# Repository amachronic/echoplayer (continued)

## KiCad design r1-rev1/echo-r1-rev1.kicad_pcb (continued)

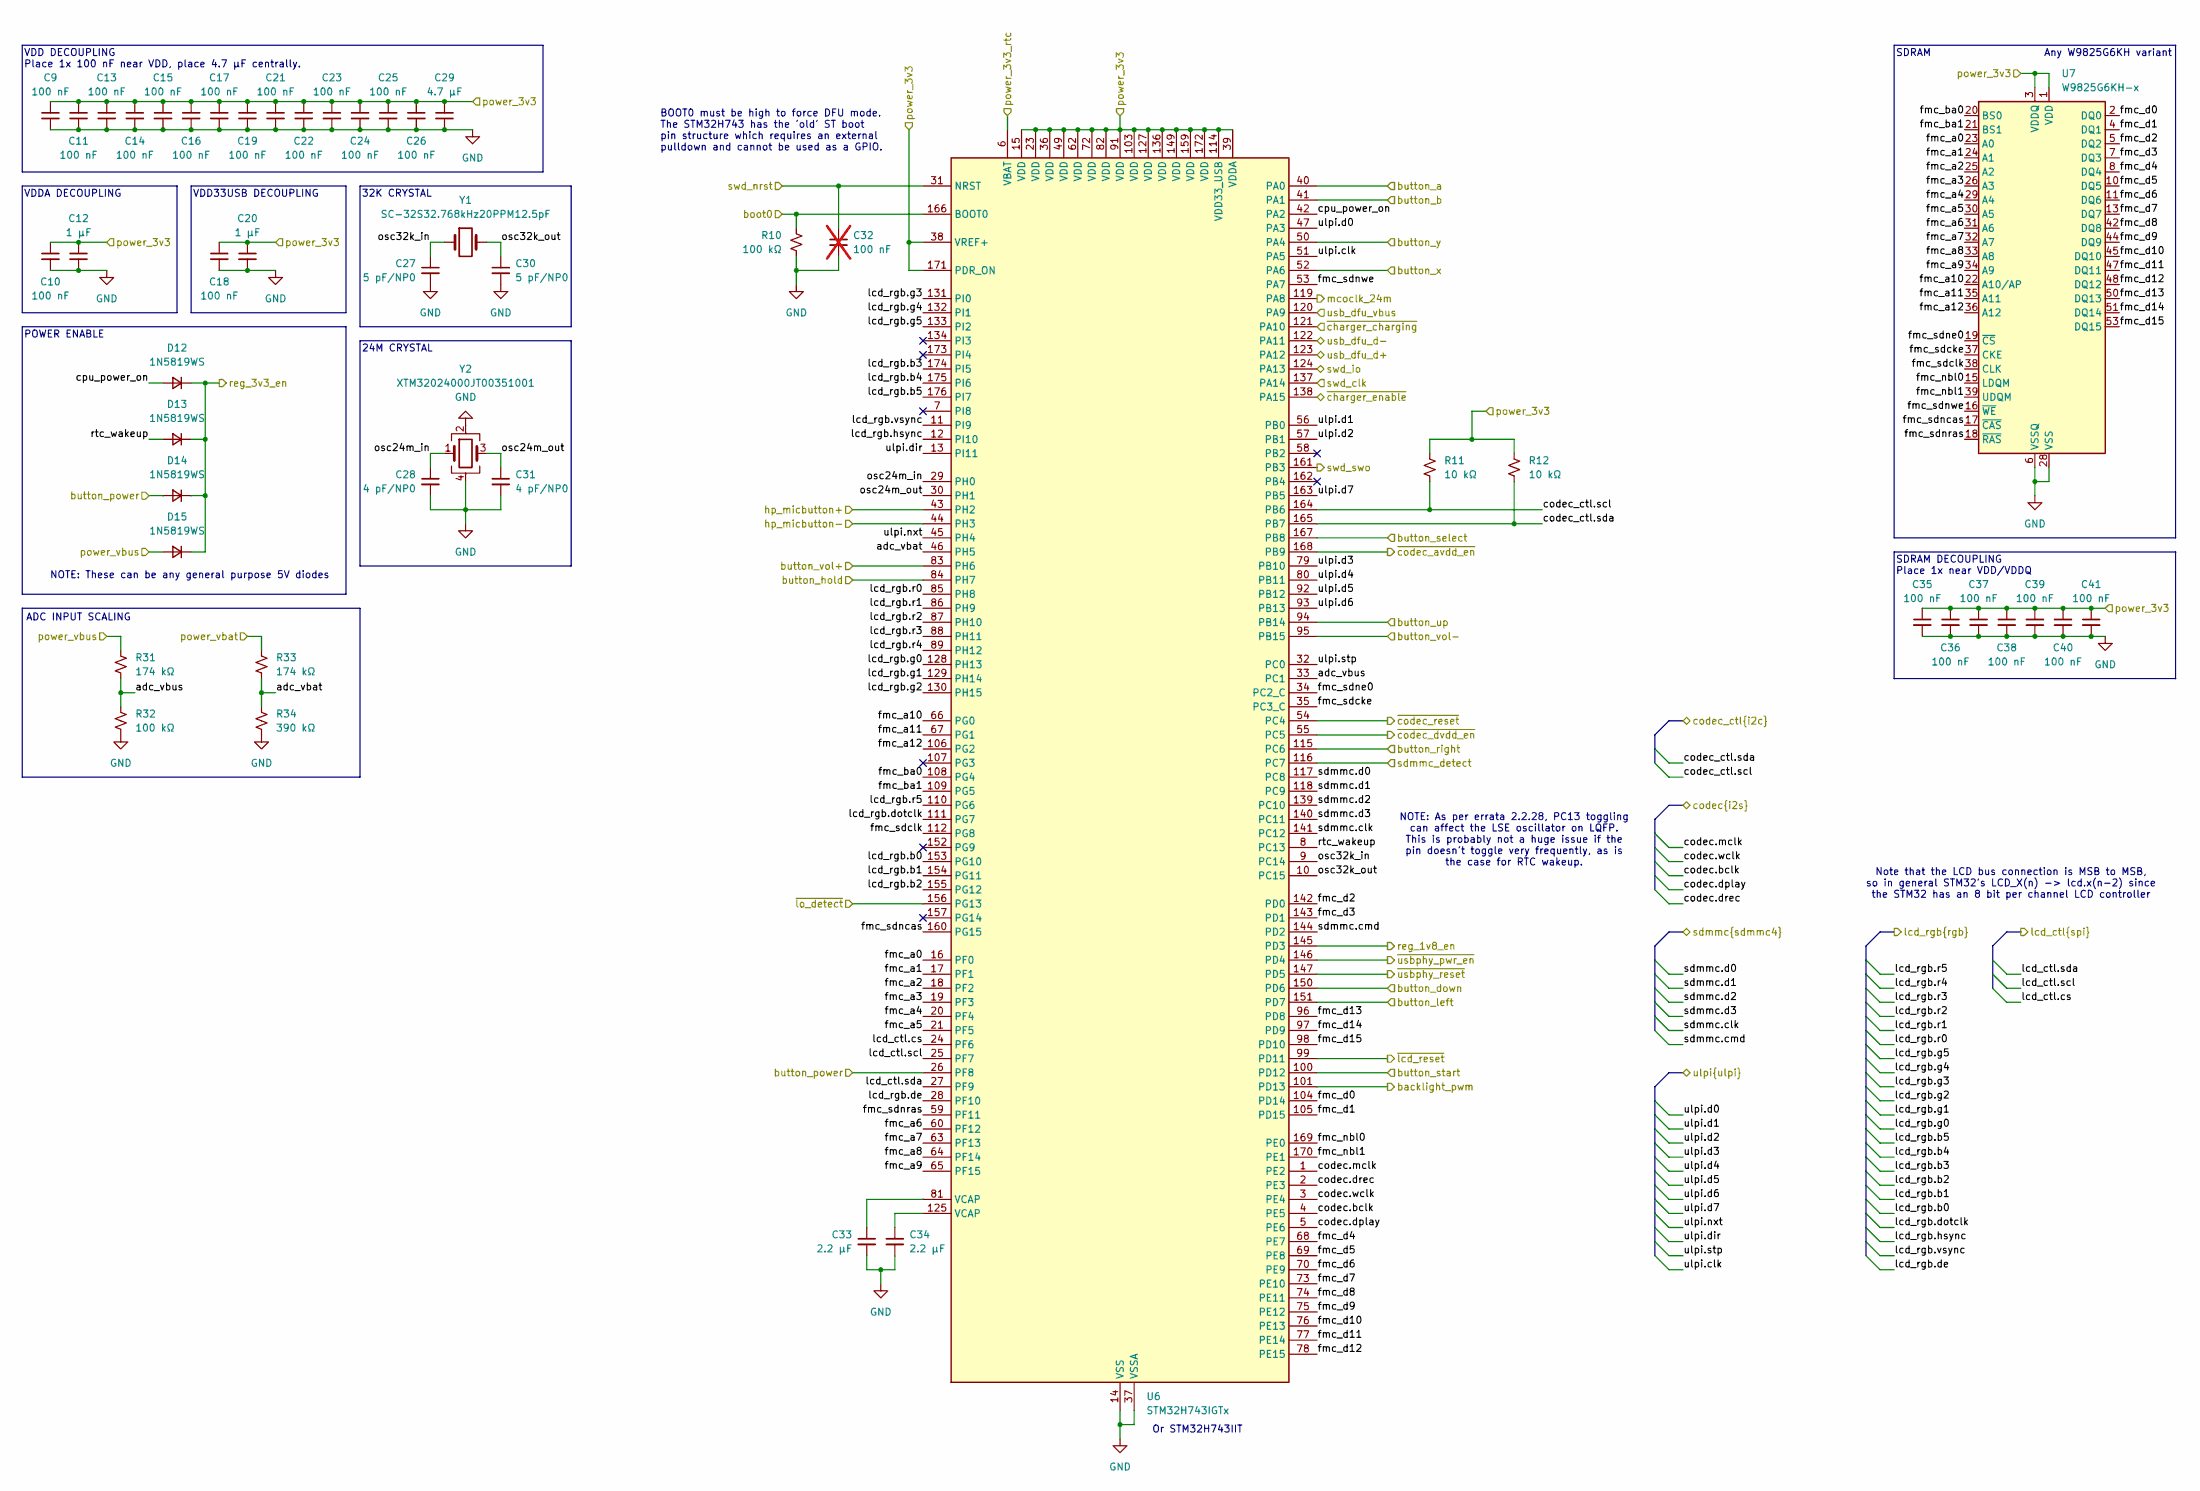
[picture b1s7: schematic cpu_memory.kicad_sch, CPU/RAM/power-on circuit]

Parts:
C9, C10, C11, C13, C14, C15, C16, C17, C18, C19, C21, C22, C23, C24, C25, C26, C35, C36, C37, C38, C39, C40, C41: 100 nF; C_0402_1005Metric; LCSC# C77020
C12, C20: 1 µF; C_0402_1005Metric; LCSC# C52923
C27, C30: 5 pF/NP0; C_0402_1005Metric; LCSC# C161328
C28, C31: 4 pF/NP0; C_0402_1005Metric; LCSC# C541337
C29: 4.7 µF; C_0603_1608Metric; LCSC# C69335
C32: 100 nF; C_0402_1005Metric; LCSC# C77020; not fitted
C33, C34: 2.2 µF; C_0603_1608Metric; LCSC# C57895
D12, D13, D14, D15: 1N5819WS; D_SOD-323; LCSC# C191023
R10, R32: 100 kΩ; R_0402_1005Metric; LCSC# C60491
R11, R12: 10 kΩ; R_0402_1005Metric; LCSC# C60490
R31, R33: 174 kΩ; R_0603_1608Metric; LCSC# C2933159
R34: 390 kΩ; R_0603_1608Metric; LCSC# C23150
U6: STM32H743IGTx; LQFP-176_24x24mm_P0.5mm; LCSC# C89597
U7: W9825G6KH-x; TSOP-II-54_22.2x10.16mm_P0.8mm; LCSC# C62246
Y1: SC-32S32.768kHz20PPM12.5pF; Crystal_SMD_3215-2Pin_3.2x1.5mm; LCSC# C97606
Y2: XTM32024000JT00351001; Crystal_SMD_3225-4Pin_3.2x2.5mm; LCSC# C37635376

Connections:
3V3: C9.1, C10.1, C11.1, C12.1, C13.1, C14.1, C15.1, C16.1, C17.1, C18.1, C19.1, C20.1, C21.1, C22.1, C23.1, C24.1, C25.1, C26.1, C29.1, C35.1, C36.1, C37.1, C38.1, C39.1, C40.1, C41.1, R11.1, R12.1, U6.15 (VDD), U6.23 (VDD), U6.36 (VDD), U6.38 (VREF+), U6.39 (VDDA), U6.49 (VDD), U6.62 (VDD), U6.72 (VDD), U6.82 (VDD), U6.91 (VDD), U6.103 (VDD), U6.114 (VDD33_USB), U6.127 (VDD), U6.136 (VDD), U6.149 (VDD), U6.159 (VDD), U6.171 (PDR_ON), U6.172 (VDD), U7.1 (VDD), U7.3 (VDDQ), U7.9 (VDDQ), U7.14 (VDD), U7.27 (VDD), U7.43 (VDDQ), U7.49 (VDDQ); also elsewhere on the board
3V3_LDO: U6.6 (VBAT); also elsewhere on the board
/audio/codec.bclk: U6.4 (PE5); also elsewhere on the board
/audio/codec.dplay: U6.5 (PE6); also elsewhere on the board
/audio/codec.drec: U6.2 (PE3); also elsewhere on the board
/audio/codec.mclk: U6.1 (PE2); also elsewhere on the board
/audio/codec.wclk: U6.3 (PE4); also elsewhere on the board
/audio/codec_ctl.scl: R11.2, U6.164 (PB6); also elsewhere on the board
/audio/codec_ctl.sda: R12.2, U6.165 (PB7); also elsewhere on the board
/audio/hp_micbutton+: U6.43 (PH2); also elsewhere on the board
/audio/hp_micbutton-: U6.44 (PH3); also elsewhere on the board
/audio/~avdd_en: U6.168 (PB9); also elsewhere on the board
/audio/~dvdd_en: U6.55 (PC5); also elsewhere on the board
/audio/~lo_detect: U6.156 (PG13); also elsewhere on the board
/audio/~reset: U6.54 (PC4); also elsewhere on the board
/button/button_a: U6.40 (PA0); also elsewhere on the board
/button/button_b: U6.41 (PA1); also elsewhere on the board
/button/button_down: U6.150 (PD6); also elsewhere on the board
/button/button_hold: U6.84 (PH7); also elsewhere on the board
/button/button_left: U6.151 (PD7); also elsewhere on the board
/button/button_power: D14.2 (A), U6.26 (PF8); also elsewhere on the board
/button/button_right: U6.115 (PC6); also elsewhere on the board
/button/button_select: R10.1, U6.166 (BOOT0), U6.167 (PB8); also elsewhere on the board
/button/button_start: U6.100 (PD12); also elsewhere on the board
/button/button_up: U6.94 (PB14); also elsewhere on the board
/button/button_vol+: U6.83 (PH6); also elsewhere on the board
/button/button_vol-: U6.95 (PB15); also elsewhere on the board
/button/button_x: U6.52 (PA6); also elsewhere on the board
/button/button_y: U6.50 (PA4); also elsewhere on the board
/cpu/adc_vbat: R33.2, R34.1, U6.46 (PH5)
/cpu/adc_vbus: R31.2, R32.1, U6.33 (PC1)
/cpu/backlight_pwm: U6.101 (PD13); also elsewhere on the board
/cpu/cpu_power_on: D12.2 (A), U6.42 (PA2)
/cpu/fmc_a0: U6.16 (PF0), U7.23 (A0)
/cpu/fmc_a1: U6.17 (PF1), U7.24 (A1)
/cpu/fmc_a2: U6.18 (PF2), U7.25 (A2)
/cpu/fmc_a3: U6.19 (PF3), U7.26 (A3)
/cpu/fmc_a4: U6.20 (PF4), U7.29 (A4)
/cpu/fmc_a5: U6.21 (PF5), U7.30 (A5)
/cpu/fmc_a6: U6.60 (PF12), U7.31 (A6)
/cpu/fmc_a7: U6.63 (PF13), U7.32 (A7)
/cpu/fmc_a8: U6.64 (PF14), U7.33 (A8)
/cpu/fmc_a9: U6.65 (PF15), U7.34 (A9)
/cpu/fmc_a10: U6.66 (PG0), U7.22 (A10/AP)
/cpu/fmc_a11: U6.67 (PG1), U7.35 (A11)
/cpu/fmc_a12: U6.106 (PG2), U7.36 (A12)
/cpu/fmc_ba0: U6.108 (PG4), U7.20 (BS0)
/cpu/fmc_ba1: U6.109 (PG5), U7.21 (BS1)
/cpu/fmc_d0: U6.104 (PD14), U7.2 (DQ0)
/cpu/fmc_d1: U6.105 (PD15), U7.4 (DQ1)
/cpu/fmc_d2: U6.142 (PD0), U7.5 (DQ2)
/cpu/fmc_d3: U6.143 (PD1), U7.7 (DQ3)
/cpu/fmc_d4: U6.68 (PE7), U7.8 (DQ4)
/cpu/fmc_d5: U6.69 (PE8), U7.10 (DQ5)
/cpu/fmc_d6: U6.70 (PE9), U7.11 (DQ6)
/cpu/fmc_d7: U6.73 (PE10), U7.13 (DQ7)
/cpu/fmc_d8: U6.74 (PE11), U7.42 (DQ8)
/cpu/fmc_d9: U6.75 (PE12), U7.44 (DQ9)
/cpu/fmc_d10: U6.76 (PE13), U7.45 (DQ10)
/cpu/fmc_d11: U6.77 (PE14), U7.47 (DQ11)
/cpu/fmc_d12: U6.78 (PE15), U7.48 (DQ12)
/cpu/fmc_d13: U6.96 (PD8), U7.50 (DQ13)
/cpu/fmc_d14: U6.97 (PD9), U7.51 (DQ14)
/cpu/fmc_d15: U6.98 (PD10), U7.53 (DQ15)
/cpu/fmc_nbl0: U6.169 (PE0), U7.15 (LDQM)
/cpu/fmc_nbl1: U6.170 (PE1), U7.39 (UDQM)
/cpu/fmc_sdcke: U6.35 (PC3_C), U7.37 (CKE)
/cpu/fmc_sdclk: U6.112 (PG8), U7.38 (CLK)
/cpu/fmc_sdncas: U6.160 (PG15), U7.17 (~CAS)
/cpu/fmc_sdne0: U6.34 (PC2_C), U7.19 (~CS)
/cpu/fmc_sdnras: U6.59 (PF11), U7.18 (~RAS)
/cpu/fmc_sdnwe: U6.53 (PA7), U7.16 (~WE)
/cpu/lcd_ctl.cs: U6.24 (PF6); also elsewhere on the board
/cpu/lcd_ctl.scl: U6.25 (PF7); also elsewhere on the board
/cpu/lcd_ctl.sda: U6.27 (PF9); also elsewhere on the board
/cpu/lcd_rgb.b0: U6.153 (PG10); also elsewhere on the board
/cpu/lcd_rgb.b1: U6.154 (PG11); also elsewhere on the board
/cpu/lcd_rgb.b2: U6.155 (PG12); also elsewhere on the board
/cpu/lcd_rgb.b3: U6.174 (PI5); also elsewhere on the board
/cpu/lcd_rgb.b4: U6.175 (PI6); also elsewhere on the board
/cpu/lcd_rgb.b5: U6.176 (PI7); also elsewhere on the board
/cpu/lcd_rgb.de: U6.28 (PF10); also elsewhere on the board
/cpu/lcd_rgb.dotclk: U6.111 (PG7); also elsewhere on the board
/cpu/lcd_rgb.g0: U6.128 (PH13); also elsewhere on the board
/cpu/lcd_rgb.g1: U6.129 (PH14); also elsewhere on the board
/cpu/lcd_rgb.g2: U6.130 (PH15); also elsewhere on the board
/cpu/lcd_rgb.g3: U6.131 (PI0); also elsewhere on the board
/cpu/lcd_rgb.g4: U6.132 (PI1); also elsewhere on the board
/cpu/lcd_rgb.g5: U6.133 (PI2); also elsewhere on the board
/cpu/lcd_rgb.hsync: U6.12 (PI10); also elsewhere on the board
/cpu/lcd_rgb.r0: U6.85 (PH8); also elsewhere on the board
/cpu/lcd_rgb.r1: U6.86 (PH9); also elsewhere on the board
/cpu/lcd_rgb.r2: U6.87 (PH10); also elsewhere on the board
/cpu/lcd_rgb.r3: U6.88 (PH11); also elsewhere on the board
/cpu/lcd_rgb.r4: U6.89 (PH12); also elsewhere on the board
/cpu/lcd_rgb.r5: U6.110 (PG6); also elsewhere on the board
/cpu/lcd_rgb.vsync: U6.11 (PI9); also elsewhere on the board
/cpu/mcoclk_24m: U6.119 (PA8); also elsewhere on the board
/cpu/osc24m_in: C28.1, U6.29 (PH0), Y2.1
/cpu/osc24m_out: C31.1, U6.30 (PH1), Y2.3
/cpu/osc32k_in: C27.1, U6.9 (PC14), Y1.1
/cpu/osc32k_out: C30.1, U6.10 (PC15), Y1.2
/cpu/reg_1v8_en: U6.145 (PD3); also elsewhere on the board
/cpu/reg_3v3_en: D12.1 (K), D13.1 (K), D14.1 (K), D15.1 (K); also elsewhere on the board
/cpu/rtc_wakeup: D13.2 (A), U6.8 (PC13)
/cpu/sdmmc.clk: U6.141 (PC12); also elsewhere on the board
/cpu/sdmmc.cmd: U6.144 (PD2); also elsewhere on the board
/cpu/sdmmc.d0: U6.117 (PC8); also elsewhere on the board
/cpu/sdmmc.d1: U6.118 (PC9); also elsewhere on the board
/cpu/sdmmc.d2: U6.139 (PC10); also elsewhere on the board
/cpu/sdmmc.d3: U6.140 (PC11); also elsewhere on the board
/cpu/sdmmc_detect: U6.116 (PC7); also elsewhere on the board
/cpu/swd_clk: U6.137 (PA14); also elsewhere on the board
/cpu/swd_io: U6.124 (PA13); also elsewhere on the board
/cpu/swd_nrst: C32.1, U6.31 (NRST); also elsewhere on the board
/cpu/swd_swo: U6.161 (PB3); also elsewhere on the board
/cpu/ulpi.clk: U6.51 (PA5); also elsewhere on the board
/cpu/ulpi.d0: U6.47 (PA3); also elsewhere on the board
/cpu/ulpi.d1: U6.56 (PB0); also elsewhere on the board
/cpu/ulpi.d2: U6.57 (PB1); also elsewhere on the board
/cpu/ulpi.d3: U6.79 (PB10); also elsewhere on the board
/cpu/ulpi.d4: U6.80 (PB11); also elsewhere on the board
/cpu/ulpi.d5: U6.92 (PB12); also elsewhere on the board
/cpu/ulpi.d6: U6.93 (PB13); also elsewhere on the board
/cpu/ulpi.d7: U6.163 (PB5); also elsewhere on the board
/cpu/ulpi.dir: U6.13 (PI11); also elsewhere on the board
/cpu/ulpi.nxt: U6.45 (PH4); also elsewhere on the board
/cpu/ulpi.stp: U6.32 (PC0); also elsewhere on the board
/cpu/usb_dfu_d+: U6.123 (PA12); also elsewhere on the board
/cpu/usb_dfu_d-: U6.122 (PA11); also elsewhere on the board
/cpu/~charger_charging: U6.121 (PA10); also elsewhere on the board
/cpu/~charger_enable: U6.138 (PA15); also elsewhere on the board
/cpu/~lcd_reset: U6.99 (PD11); also elsewhere on the board
/cpu/~usbphy_pwr_en: U6.146 (PD4); also elsewhere on the board
/cpu/~usbphy_reset: U6.147 (PD5); also elsewhere on the board
GND: C9.2, C10.2, C11.2, C12.2, C13.2, C14.2, C15.2, C16.2, C17.2, C18.2, C19.2, C20.2, C21.2, C22.2, C23.2, C24.2, C25.2, C26.2, C27.2, C28.2, C29.2, C30.2, C31.2, C32.2, C33.2, C34.2, C35.2, C36.2, C37.2, C38.2, C39.2, C40.2, C41.2, R10.2, R32.2, R34.2, U6.14 (VSS), U6.22 (VSS), U6.37 (VSSA), U6.48 (VSS), U6.61 (VSS), U6.71 (VSS), U6.90 (VSS), U6.102 (VSS), U6.113 (VSS), U6.126 (VSS), U6.135 (VSS), U6.148 (VSS), U6.158 (VSS), U7.6 (VSSQ), U7.12 (VSSQ), U7.28 (VSS), U7.41 (VSS), U7.46 (VSSQ), U7.52 (VSSQ), U7.54 (VSS), Y2.2, Y2.4; also elsewhere on the board
unnamed: C33.1, U6.81 (VCAP)
unnamed: C34.1, U6.125 (VCAP)
VBAT: R33.1; also elsewhere on the board
VBUS: D15.2 (A), R31.1, U6.120 (PA9); also elsewhere on the board

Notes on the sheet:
32K CRYSTAL
SDRAM DECOUPLING Place 1x near VDD/VDDQ
Note that the LCD bus connection is MSB to MSB, so in general STM32's LCD_X(n) -> lcd.x(n-2) since the STM32 has an 8 bit per channel LCD controller
BOOT0 must be high to force DFU mode. The STM32H743 has the 'old' ST boot pin structure which requires an external pulldown and cannot be used as a GPIO.
Or STM32H743IIT
NOTE: These can be any general purpose 5V diodes
ADC INPUT SCALING
VDD33USB DECOUPLING
NOTE: As per errata 2.2.28, PC13 toggling can affect the LSE oscillator on LQFP. This is probably not a huge issue if the pin doesn't toggle very frequently, as is the case for RTC wakeup.
VDD DECOUPLING Place 1x 100 nF near VDD, place 4.7 µF centrally.
VDDA DECOUPLING
24M CRYSTAL
SDRAM
POWER ENABLE
Any W9825G6KH variant

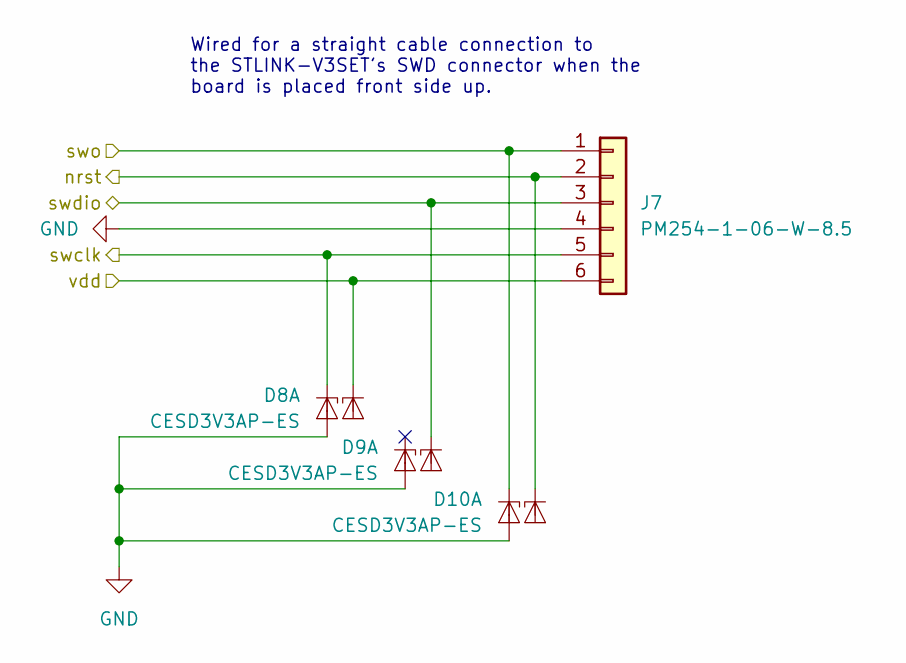
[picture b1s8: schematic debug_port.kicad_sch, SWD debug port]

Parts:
D8, D9, D10: CESD3V3AP-ES; SOT-23; LCSC# C5199223
J7: PM254-1-06-W-8.5; PinSocket_1x06_P2.54mm_Horizontal; LCSC# C2897388

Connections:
3V3: D8.2 (K2), J7.6; also elsewhere on the board
/cpu/swd_clk: D8.1 (K1), J7.5; also elsewhere on the board
/cpu/swd_io: D9.2 (K2), J7.3; also elsewhere on the board
/cpu/swd_nrst: D10.2 (K2), J7.2; also elsewhere on the board
/cpu/swd_swo: D10.1 (K1), J7.1; also elsewhere on the board
GND: D8.3 (A), D9.3 (A), D10.3 (A), J7.4; also elsewhere on the board

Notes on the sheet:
Wired for a straight cable connection to the STLINK-V3SET's SWD connector when the board is placed front side up.

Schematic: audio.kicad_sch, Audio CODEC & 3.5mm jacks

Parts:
C46, C48, C50, C53: 100 nF; C_0402_1005Metric; LCSC# C77020
C47, C49, C51, C54: 10 µF; C_0603_1608Metric; LCSC# C91606
C52: 10 nF/NP0; C_0603_1608Metric; LCSC# C85973
C55, C56: 10 µF; CP_Elec_4x5.4; LCSC# C72485
D5: PESD3V3L2BT; SOT-23; LCSC# C2923380
D6, D7, D11: CESD3V3AP-ES; SOT-23; LCSC# C5199223
J4: HP_3.5mm; Jack_3.5mm_HCTL_HC-PJ-320A-4P-D; LCSC# C5372851
J5: LO_3.5mm; Jack_3.5mm_HCTL_HC-PJ-320A-4P-D; LCSC# C5372851
NT1, NT2: NetTie_2; NetTie_0.15mm_SMD
Q6, Q7: AO3401A; SOT-23; LCSC# C347476
R20, R21, R22, R26: 100 kΩ; R_0402_1005Metric; LCSC# C60491
R23: 2.2 kΩ; R_0402_1005Metric; LCSC# C114762
R25: 1 MΩ; R_0402_1005Metric; LCSC# C138033
U9: TLV320AIC3104; Texas_RHB0032E_VQFN-32-1EP_5x5mm_P0.5mm_EP3.45x3.45mm_Therm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; LCSC# C181753

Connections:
1V8: Q7.2 (S), R22.1; also elsewhere on the board
3V3: C48.1, C49.1, U9.7 (IOVDD); also elsewhere on the board
3V3_LDO: Q6.2 (S), R21.1, R25.1; also elsewhere on the board
/audio/avdd: C50.1, C51.1, C53.1, C54.1, Q6.3 (D), U9.18 (DRVDD), U9.24 (DRVDD), U9.25 (AVDD)
/audio/codec.bclk: U9.2 (BCLK); also elsewhere on the board
/audio/codec.dplay: U9.4 (DIN); also elsewhere on the board
/audio/codec.drec: U9.5 (DOUT); also elsewhere on the board
/audio/codec.mclk: U9.1 (MCLK); also elsewhere on the board
/audio/codec.wclk: U9.3 (WCLK); also elsewhere on the board
/audio/codec_ctl.scl: U9.8 (SCL); also elsewhere on the board
/audio/codec_ctl.sda: U9.9 (SDA); also elsewhere on the board
/audio/dvdd: C46.1, C47.1, Q7.3 (D), U9.32 (DVDD)
/audio/hp_com: D7.1 (K1), J4.T, NT2.2, U9.20 (HPLCOM), U9.22 (HPRCOM)
/audio/hp_left: D6.1 (K1), J4.R1, U9.19 (HPLOUT)
/audio/hp_mic: C52.1, D7.2 (K2), J4.S, NT1.2, R23.2, U9.14 (MIC2L/LINE2L/MICDET)
/audio/hp_micbutton+: NT1.1; also elsewhere on the board
/audio/hp_micbutton-: NT2.1; also elsewhere on the board
/audio/hp_right: D6.2 (K2), J4.R2, U9.23 (HPROUT)
/audio/lo_left: C55.1, U9.27 (LEFT_LOP)
/audio/lo_right: C56.1, U9.29 (RIGHT_LOP)
/audio/micbias: R23.1, U9.15 (MICBIAS)
/audio/~avdd_en: Q6.1 (G), R21.2; also elsewhere on the board
/audio/~dvdd_en: Q7.1 (G), R22.2; also elsewhere on the board
/audio/~lo_detect: R26.1; also elsewhere on the board
/audio/~reset: R20.1, U9.31 (~RESET); also elsewhere on the board
GND: C46.2, C47.2, C48.2, C49.2, C50.2, C51.2, C53.2, C54.2, D5.3 (GND), D6.3 (A), D7.3 (A), D11.3 (A), J5.T, R20.2, U9.6 (DVSS), U9.10 (MIC1LP/LINE1LP), U9.11 (MIC1LM/LINE1LM), U9.12 (MIC1RP/LINE1RM), U9.13 (MIC1RM/LINE1RM), U9.17 (AVSS1), U9.21 (DRVSS), U9.26 (AVSS2), U9.33 (DRVSS); also elsewhere on the board
unnamed: C56.2, D5.1 (IO1), J5.R2
unnamed: C55.2, D5.2 (IO2), J5.R1
unnamed: D11.2 (K2), J5.S, R25.2, R26.2
unnamed: C52.2, U9.16 (MIC2R/LINE2R)

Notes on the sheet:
HEADPHONE JACK
CODEC AVDD DECOUPLING
CODEC AVDD/DRVDD SWITCH
CODEC DRVDD DECOUPLING Place near pin 24
/!\ WARNING /!\ These jacks jave a wrong, nonstandard pinout and don't work with normal equipment. To get audio you need to construct a 4-pin TRRS male-to-female adapter. CTIA wiring diagram: (Player) <-> (Adapter) Tip <-> Ring2 Ring1 <-> Tip Ring2 <-> Ring1 Sleeve <-> Sleeve
Headphone detection is done over I2C using the codec's inbuilt detection function
CODEC DVDD DECOUPLING
LINE-OUT JACK
CODEC IOVDD DECOUPLING
Since the jack's ground is HPCOM (1.35V), micbias should always be connected to AVDD (3.3V) to give a sufficient bias voltage.
AUDIO CODEC
Recommended power sequencing: 1. IOVDD first 2. AVDD/DRVDD second 3. DVDD last and within 5ms of AVDD rise 4. ~{RESET} held low until all supplies stable.
CODEC DVDD SWITCH

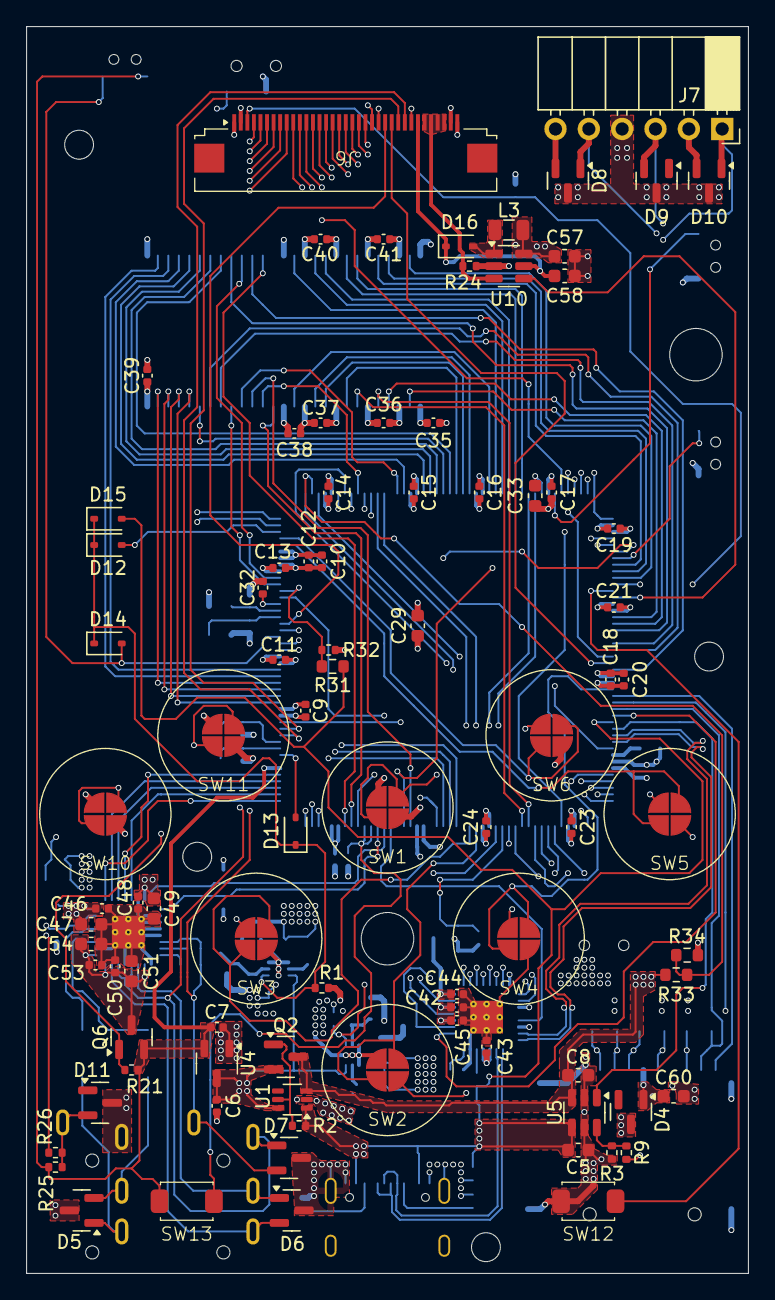
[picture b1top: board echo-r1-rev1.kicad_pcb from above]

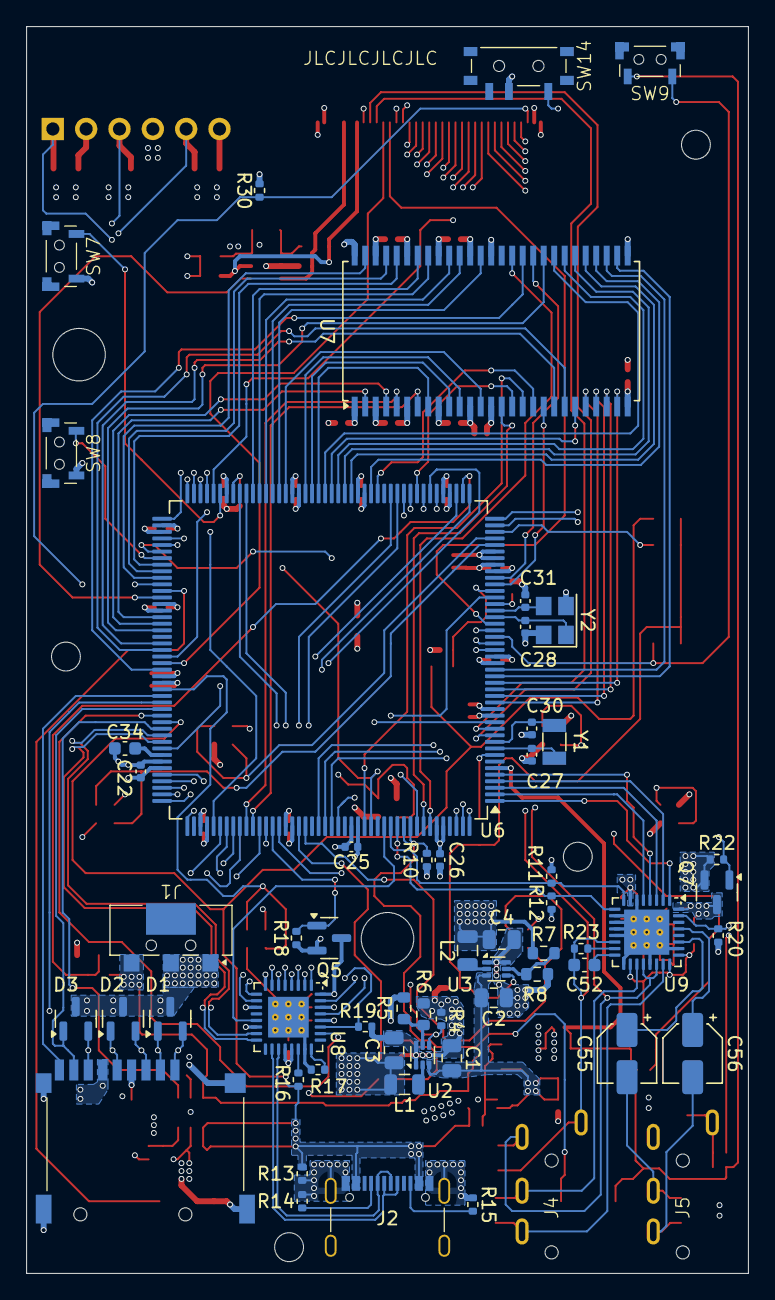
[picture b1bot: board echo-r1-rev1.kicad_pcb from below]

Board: 6 copper layers, 55.0 x 95.0 mm, 154 parts (58 on the bottom side), 171 nets.

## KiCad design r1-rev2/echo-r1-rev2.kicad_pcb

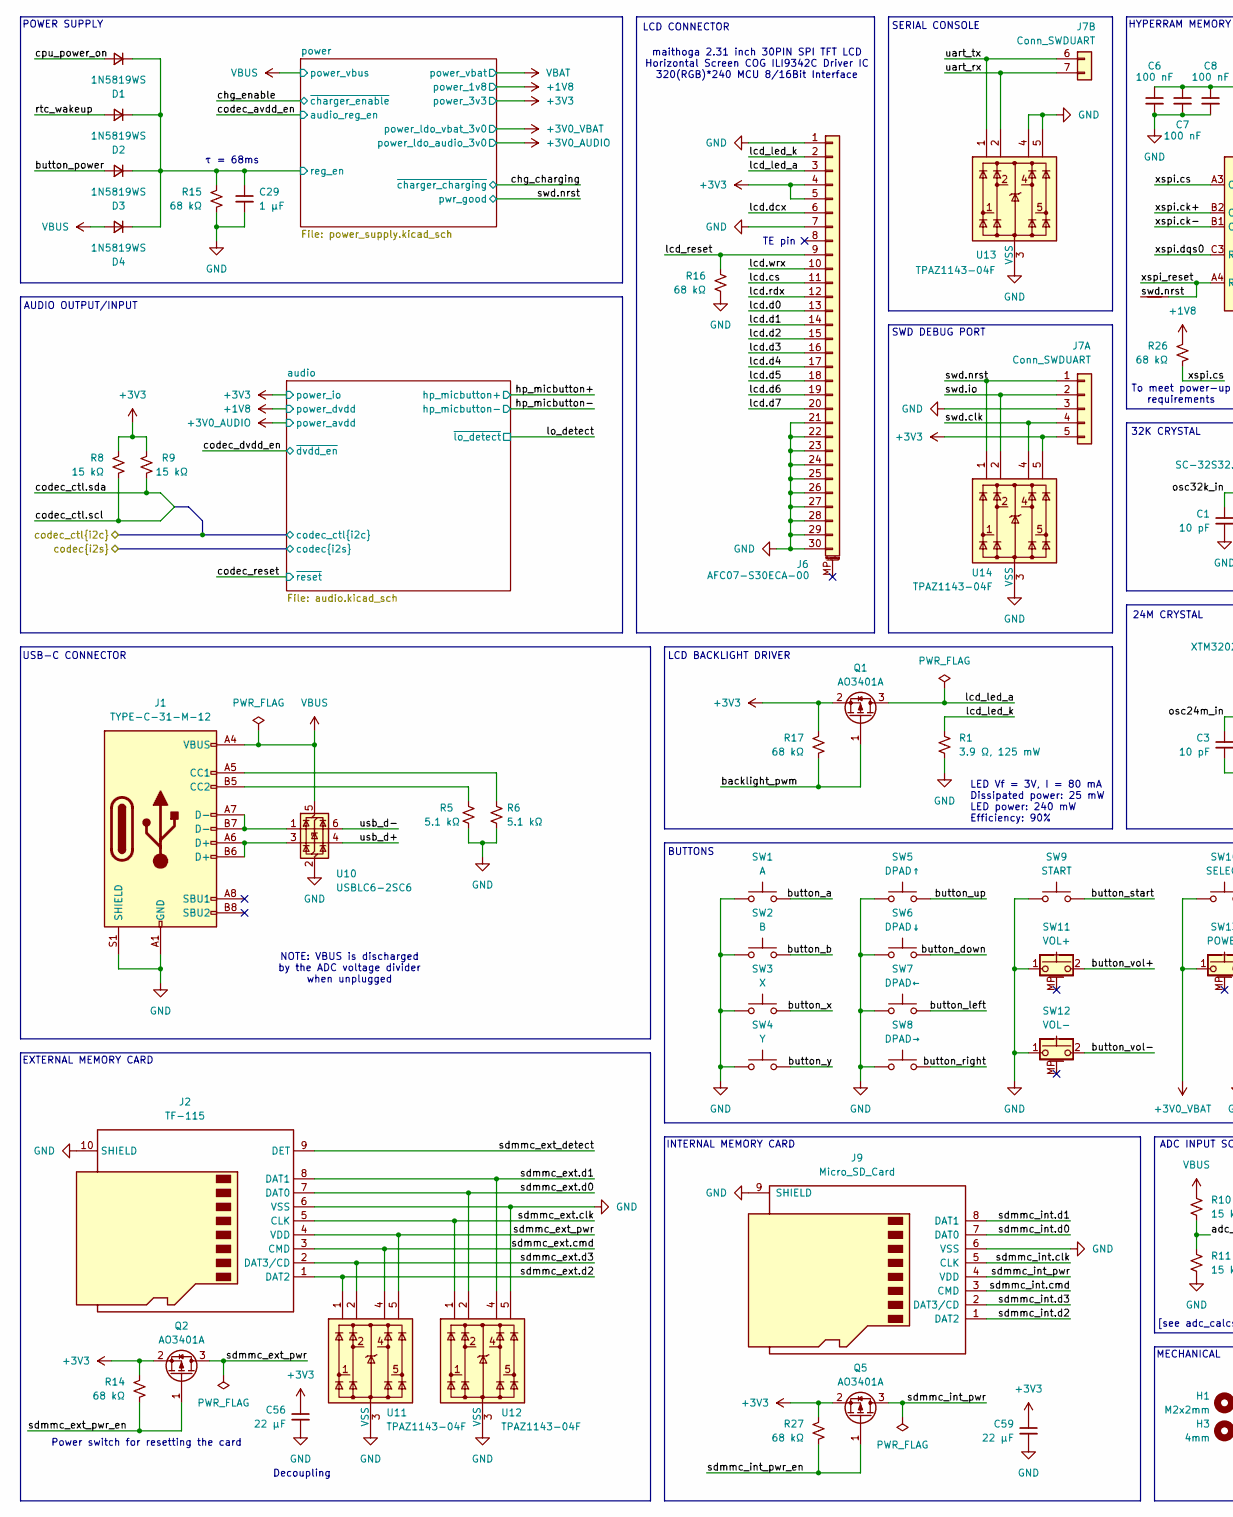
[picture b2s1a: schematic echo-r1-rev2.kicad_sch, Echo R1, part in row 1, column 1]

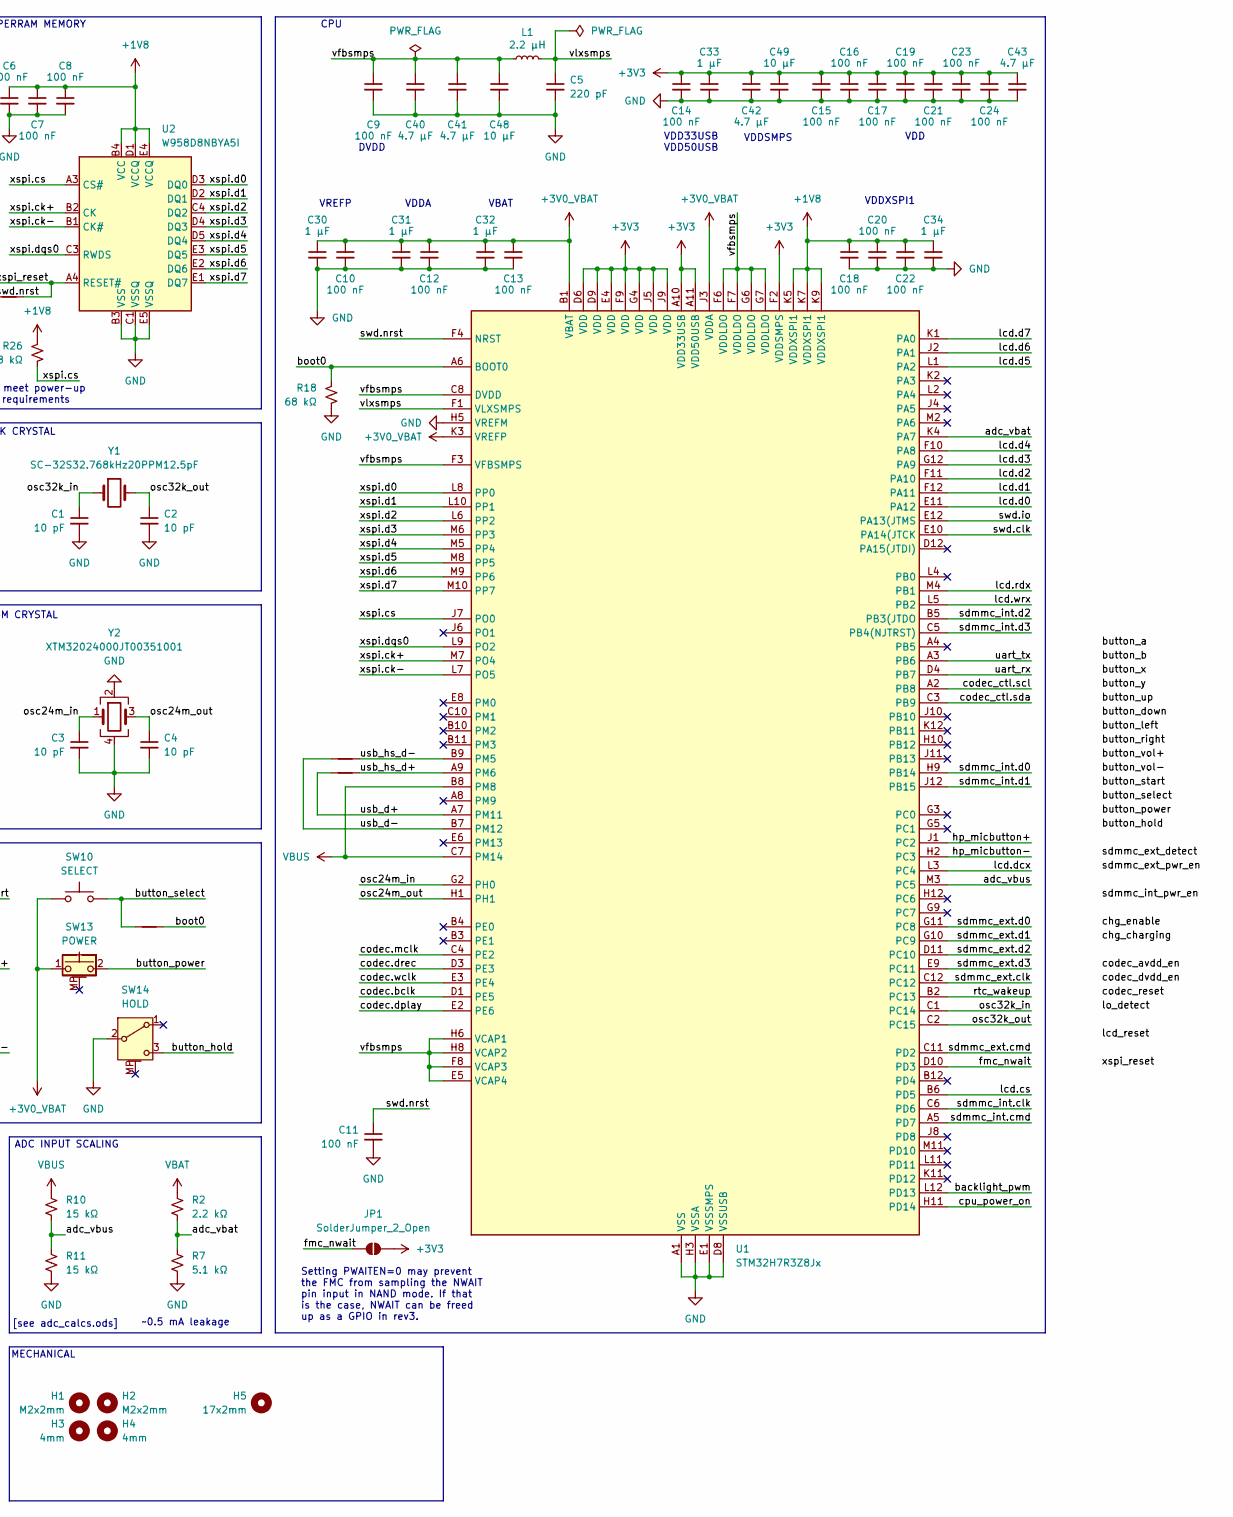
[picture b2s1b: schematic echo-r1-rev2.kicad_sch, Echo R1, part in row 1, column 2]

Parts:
C1, C2, C3, C4: 10 pF; C_0402_1005Metric
C5: 220 pF; C_0402_1005Metric
C6, C7, C8, C9, C10, C11, C12, C13, C14, C15, C16, C17, C18, C19, C20, C21, C22, C23, C24: 100 nF; C_0402_1005Metric
C29, C30, C31, C32, C33, C34: 1 µF; C_0402_1005Metric
C40, C41, C42, C43: 4.7 µF; C_0805_2012Metric
C48, C49: 10 µF; C_0805_2012Metric
C56, C59: 22 µF; C_0805_2012Metric
D1, D2, D3, D4: 1N5819WS; D_SOD-323
H1, H2: M2x2mm; MountingHole_2.2mm_M2
H3, H4: 4mm; MountingHole_4mm
H5: 17x2mm; Slot_17x2mm
J1: TYPE-C-31-M-12; USB_C-Hroparts-TYPE-C-31-M-12
J2: TF-115; microSD_XUNPU_TF-115
J6: AFC07-S30ECA-00; Conn_Jushuo_AFC07-S30ECA-00_RTL
J7: Conn_SWDUART; PinHeader_1x07_P2.54mm_Vertical
J9: Micro_SD_Card; microSD_XUNPU_TF-102-15
JP1: SolderJumper_2_Open; SolderJumper-2_P1.3mm_Open_RoundedPad1.0x1.5mm
L1: 2.2 µH; L_Changjiang_FNR3015S
NT1, NT2: NetTie_2; NetTie_0.15mm_SMD
NT3, NT4: NetTie_2; NetTie_0.10mm_SMD
Q1, Q2, Q5: AO3401A; SOT-23
R1: 3.9 Ω, 125 mW; R_0805_2012Metric
R2: 2.2 kΩ; R_0402_1005Metric
R5, R6, R7: 5.1 kΩ; R_0402_1005Metric
R8, R9, R10, R11: 15 kΩ; R_0402_1005Metric
R14, R15, R16, R17, R18, R26, R27: 68 kΩ; R_0402_1005Metric
SW1: A; Switch_SHOUHAN_TS3735PA
SW2: B; Switch_SHOUHAN_TS3735PA
SW3: X; Switch_SHOUHAN_TS3735PA
SW4: Y; Switch_SHOUHAN_TS3735PA
SW5: DPAD↑; Switch_SHOUHAN_TS3735PA
SW6: DPAD↓; Switch_SHOUHAN_TS3735PA
SW7: DPAD←; Switch_SHOUHAN_TS3735PA
SW8: DPAD→; Switch_SHOUHAN_TS3735PA
SW9: START; Switch_SHOUHAN_TS3735PA
SW10: SELECT; Switch_SHOUHAN_TS3735PA
SW11: VOL+; Switch_HROPARTS_K2-1112SA-A4DW-01
SW12: VOL-; Switch_HROPARTS_K2-1112SA-A4DW-01
SW13: POWER; Switch_HROPARTS_K2-1112SA-A4DW-01
SW14: HOLD; Switch_SHOUHAN_MSK12C02-HB
U1: STM32H7R3Z8Jx; UFBGA-144_10x10mm_Layout12x12_P0.8mm
U2: W958D8NBYA5I; TFBGA-24_6x8mm_Layout5x5_P1.0mm_Ball0.4mm
U10: USBLC6-2SC6; SOT-23-6
U11, U12, U13, U14: TPAZ1143-04F; TECHPUBLIC_UDFN-10_1.0x2.5mm_P0.5mm
Y1: SC-32S32.768kHz20PPM12.5pF; Crystal_SMD_3215-2Pin_3.2x1.5mm
Y2: XTM32024000JT00351001; Crystal_SMD_3225-4Pin_3.2x2.5mm

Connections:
+1V8: C6.1, C7.1, C8.1, C18.1, C20.1, C22.1, C34.1, R26.1, U1.K5 (VDDXSPI1), U1.K7 (VDDXSPI1), U1.K9 (VDDXSPI1), U2.B4 (VCC), U2.D1 (VCCQ), U2.E4 (VCCQ); also elsewhere on the board
+3V0_VBAT: C10.1, C12.1, C13.1, C30.1, C31.1, C32.1, SW10.1, SW13.1, U1.B1 (VBAT), U1.J3 (VDDA), U1.K3 (VREFP); also elsewhere on the board
+3V3: C14.1, C15.1, C16.1, C17.1, C19.1, C21.1, C23.1, C24.1, C33.1, C42.1, C43.1, C49.1, C56.1, C59.1, J6.4, J6.5, J7.5, JP1.2 (B), Q1.2 (S), Q2.2 (S), Q5.2 (S), R8.1, R9.1, R14.1, R17.1, R27.1, U1.A10 (VDD33USB), U1.A11 (VDD50USB), U1.D6 (VDD), U1.D9 (VDD), U1.E4 (VDD), U1.F2 (VDDSMPS), U1.F9 (VDD), U1.G4 (VDD), U1.J5 (VDD), U1.J9 (VDD), U14.5; also elsewhere on the board
/adc_vbat: R2.2, R7.1, U1.K4 (PA7)
/adc_vbus: R10.1, R11.1, U1.M3 (PC5)
/backlight_pwm: Q1.1 (G), R17.2, U1.L12 (PD13)
/boot0: NT2.2, R18.1, U1.A6 (BOOT0)
/button_a: SW1.2
/button_b: SW2.2
/button_down: SW6.2
/button_hold: SW14.3 (C)
/button_left: SW7.2
/button_power: D3.2 (A), SW13.2
/button_right: SW8.2
/button_select: NT2.1, SW10.2
/button_start: SW9.2
/button_up: SW5.2
/button_vol+: SW11.2
/button_vol-: SW12.2
/button_x: SW3.2
/button_y: SW4.2
/codec.bclk: U1.D1 (PE5); also elsewhere on the board
/codec.dplay: U1.E2 (PE6); also elsewhere on the board
/codec.drec: U1.D3 (PE3); also elsewhere on the board
/codec.mclk: U1.C4 (PE2); also elsewhere on the board
/codec.wclk: U1.E3 (PE4); also elsewhere on the board
/codec_ctl.scl: R8.2, U1.A2 (PB8); also elsewhere on the board
/codec_ctl.sda: R9.2, U1.C3 (PB9); also elsewhere on the board
/cpu_power_on: D1.2 (A), U1.H11 (PD14)
/fmc_nwait: JP1.1 (A), U1.D10 (PD3)
/hp_micbutton+: U1.J1 (PC2); also elsewhere on the board
/hp_micbutton-: U1.H2 (PC3); also elsewhere on the board
/lcd.cs: J6.11, U1.B6 (PD5)
/lcd.d0: J6.13, U1.E11 (PA12)
/lcd.d1: J6.14, U1.F12 (PA11)
/lcd.d2: J6.15, U1.F11 (PA10)
/lcd.d3: J6.16, U1.G12 (PA9)
/lcd.d4: J6.17, U1.F10 (PA8)
/lcd.d5: J6.18, U1.L1 (PA2)
/lcd.d6: J6.19, U1.J2 (PA1)
/lcd.d7: J6.20, U1.K1 (PA0)
/lcd.dcx: J6.6, U1.L3 (PC4)
/lcd.rdx: J6.12, U1.M4 (PB1)
/lcd.wrx: J6.10, U1.L5 (PB2)
/lcd_led_a: J6.3, Q1.3 (D)
/lcd_led_k: J6.2, R1.1
/lcd_reset: J6.9, R16.1
/osc24m_in: C3.1, U1.G2 (PH0), Y2.1
/osc24m_out: C4.1, U1.H1, Y2.3
/osc32k_in: C1.1, U1.C1 (PC14), Y1.1
/osc32k_out: C2.1, U1.C2 (PC15), Y1.2
/power/reg_en: C29.1, D1.1 (K), D2.1 (K), D3.1 (K), D4.1 (K), R15.1; also elsewhere on the board
/rtc_wakeup: D2.2 (A), U1.B2 (PC13)
/sdmmc_ext.clk: J2.5 (CLK), U1.C12, U12.1
/sdmmc_ext.cmd: J2.3 (CMD), U1.C11 (PD2), U11.4
/sdmmc_ext.d0: J2.7 (DAT0), U1.G11 (PC8), U12.2
/sdmmc_ext.d1: J2.8 (DAT1), U1.G10 (PC9), U12.4
/sdmmc_ext.d2: J2.1 (DAT2), U1.D11 (PC10), U11.1
/sdmmc_ext.d3: J2.2 (DAT3/CD), U1.E9 (PC11), U11.2
/sdmmc_ext_detect: J2.9 (DET)
/sdmmc_ext_pwr: J2.4 (VDD), Q2.3 (D), U11.5
/sdmmc_ext_pwr_en: Q2.1 (G), R14.2
/sdmmc_int.clk: J9.5 (CLK), U1.C6 (PD6)
/sdmmc_int.cmd: J9.3 (CMD), U1.A5 (PD7)
/sdmmc_int.d0: J9.7 (DAT0), U1.H9 (PB14)
/sdmmc_int.d1: J9.8 (DAT1), U1.J12 (PB15)
/sdmmc_int.d2: J9.1 (DAT2), U1.B5 (PB3(JTDO)
/sdmmc_int.d3: J9.2 (DAT3/CD), U1.C5 (PB4(NJTRST))
/sdmmc_int_pwr: J9.4 (VDD), Q5.3 (D)
/sdmmc_int_pwr_en: Q5.1 (G), R27.2
/swd.clk: J7.4, U1.E10 (PA14(JTCK), U14.4
/swd.io: J7.2, U1.E12 (PA13(JTMS), U14.2
/swd.nrst: C11.1, J7.1, NT1.1, U1.F4 (NRST), U14.1; also elsewhere on the board
/uart_rx: J7.7 (Pin_2), U1.D4 (PB7), U13.2
/uart_tx: J7.6 (Pin_1), U1.A3 (PB6), U13.1
/usb_d+: NT4.1, U1.A7 (PM11), U10.4 (I/O2)
/usb_d-: NT3.1, U1.B7 (PM12), U10.6 (I/O1)
/usb_hs_d+: NT4.2, U1.A9 (PM6)
/usb_hs_d-: NT3.2, U1.B9 (PM5)
/vfbsmps: C9.1, C40.1, C41.1, C48.1, L1.1, U1.C8 (DVDD), U1.E5 (VCAP4), U1.F3 (VFBSMPS), U1.F6 (VDDLDO), U1.F7 (VDDLDO), U1.F8 (VCAP3), U1.G6 (VDDLDO), U1.G7 (VDDLDO), U1.H6 (VCAP1), U1.H8 (VCAP2)
/vlxsmps: C5.1, L1.2, U1.F1 (VLXSMPS)
/xspi.ck+: U1.M7 (PO4), U2.B2 (CK)
/xspi.ck-: U1.L7 (PO5), U2.B1 (CK#)
/xspi.cs: R26.2, U1.J7 (PO0), U2.A3 (CS#)
/xspi.d0: U1.L8 (PP0), U2.D3 (DQ0)
/xspi.d1: U1.L10 (PP1), U2.D2 (DQ1)
/xspi.d2: U1.L6 (PP2), U2.C4 (DQ2)
/xspi.d3: U1.M6 (PP3), U2.D4 (DQ3)
/xspi.d4: U1.M5 (PP4), U2.D5 (DQ4)
/xspi.d5: U1.M8 (PP5), U2.E3 (DQ5)
/xspi.d6: U1.M9 (PP6), U2.E2 (DQ6)
/xspi.d7: U1.M10 (PP7), U2.E1 (DQ7)
/xspi.dqs0: U1.L9 (PO2), U2.C3 (RWDS)
/xspi_reset: NT1.2, U2.A4 (RESET#)
GND: C1.2, C2.2, C3.2, C4.2, C5.2, C6.2, C7.2, C8.2, C9.2, C10.2, C11.2, C12.2, C13.2, C14.2, C15.2, C16.2, C17.2, C18.2, C19.2, C20.2, C21.2, C22.2, C23.2, C24.2, C29.2, C30.2, C31.2, C32.2, C33.2, C34.2, C40.2, C41.2, C42.2, C43.2, C48.2, C49.2, C56.2, C59.2, J1.A1 (GND), J1.A12 (GND), J1.B1 (GND), J1.B12 (GND), J1.S1 (SHIELD), J2.6 (VSS), J2.10 (SHIELD), J6.1, J6.7, J6.21, J6.22, J6.23, J6.24, J6.25, J6.26, J6.27, J6.28, J6.29, J6.30, J7.3, J9.6 (VSS), J9.9 (SHIELD), R1.2, R5.1, R6.1, R7.2, R11.2, R15.2, R16.2, R18.2, SW1.1, SW2.1, SW3.1, SW4.1, SW5.1, SW6.1, SW7.1, SW8.1, SW9.1, SW11.1, SW12.1, SW14.2 (B), U1.A1 (VSS), U1.A12 (VSS), U1.C9 (VSS), U1.D2 (VSS), U1.D5 (VSS), U1.D7 (VSS), U1.D8 (VSSUSB), U1.E1 (VSSSMPS), U1.E7 (VSS), U1.F5 (VSS), U1.G1 (VSS), U1.G8 (VSS), U1.H3 (VSSA), U1.H4 (VSS), U1.H5 (VREFM), U1.H7 (VSS), U1.K6 (VSS), U1.K8 (VSS), U1.K10 (VSS), U1.M1 (VSS), U1.M12 (VSS), U2.B3 (VSS), U2.C1 (VSSQ), U2.E5 (VSSQ), U10.2 (GND), U11.3 (VSS), U11.6 (NC), U11.7 (NC), U11.8 (VSS), U11.9 (NC), U11.10 (NC), U12.3 (VSS), U12.5, U12.6 (NC), U12.7 (NC), U12.8 (VSS), U12.9 (NC), U12.10 (NC), U13.3 (VSS), U13.4, U13.5, U13.6 (NC), U13.7 (NC), U13.8 (VSS), U13.9 (NC), U13.10 (NC), U14.3 (VSS), U14.6 (NC), U14.7 (NC), U14.8 (VSS), U14.9 (NC), U14.10 (NC), Y2.2, Y2.4; also elsewhere on the board
unnamed: J1.A5 (CC1), R6.2
unnamed: J1.B5 (CC2), R5.2
unnamed: J1.A6 (D+), J1.B6 (D+), U10.3 (I/O2)
unnamed: J1.A7 (D-), J1.B7 (D-), U10.1 (I/O1)
VBAT: R2.1; also elsewhere on the board
VBUS: D4.2 (A), J1.A4 (VBUS), J1.A9 (VBUS), J1.B4 (VBUS), J1.B9 (VBUS), R10.2, U1.B8 (PM8), U1.C7 (PM14), U10.5 (VBUS); also elsewhere on the board

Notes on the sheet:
CPU
Decoupling
BUTTONS
VDDSMPS
VDD33USB VDD50USB
SERIAL CONSOLE
VDD
maithoga 2.31 inch 30PIN SPI TFT LCD Horizontal Screen COG ILI9342C Driver IC 320(RGB)*240 MCU 8/16Bit Interface
To meet power-up requirements
[see adc_calcs.ods]
MECHANICAL
ADC INPUT SCALING
TE pin
LED Vf = 3V, I = 80 mA Dissipated power: 25 mW LED power: 240 mW Efficiency: 90%
LCD CONNECTOR
Power switch for resetting the card
LCD BACKLIGHT DRIVER
τ = 68ms
VDDXSPI1
DVDD
EXTERNAL MEMORY CARD
24M CRYSTAL
USB-C CONNECTOR
Setting PWAITEN=0 may prevent the FMC from sampling the NWAIT pin input in NAND mode. If that is the case, NWAIT can be freed up as a GPIO in rev3.
VBAT
NOTE: VBUS is discharged by the ADC voltage divider when unplugged
VREFP
POWER SUPPLY
VDDA
32K CRYSTAL
SWD DEBUG PORT
HYPERRAM MEMORY
AUDIO OUTPUT/INPUT
INTERNAL MEMORY CARD
~0.5 mA leakage
